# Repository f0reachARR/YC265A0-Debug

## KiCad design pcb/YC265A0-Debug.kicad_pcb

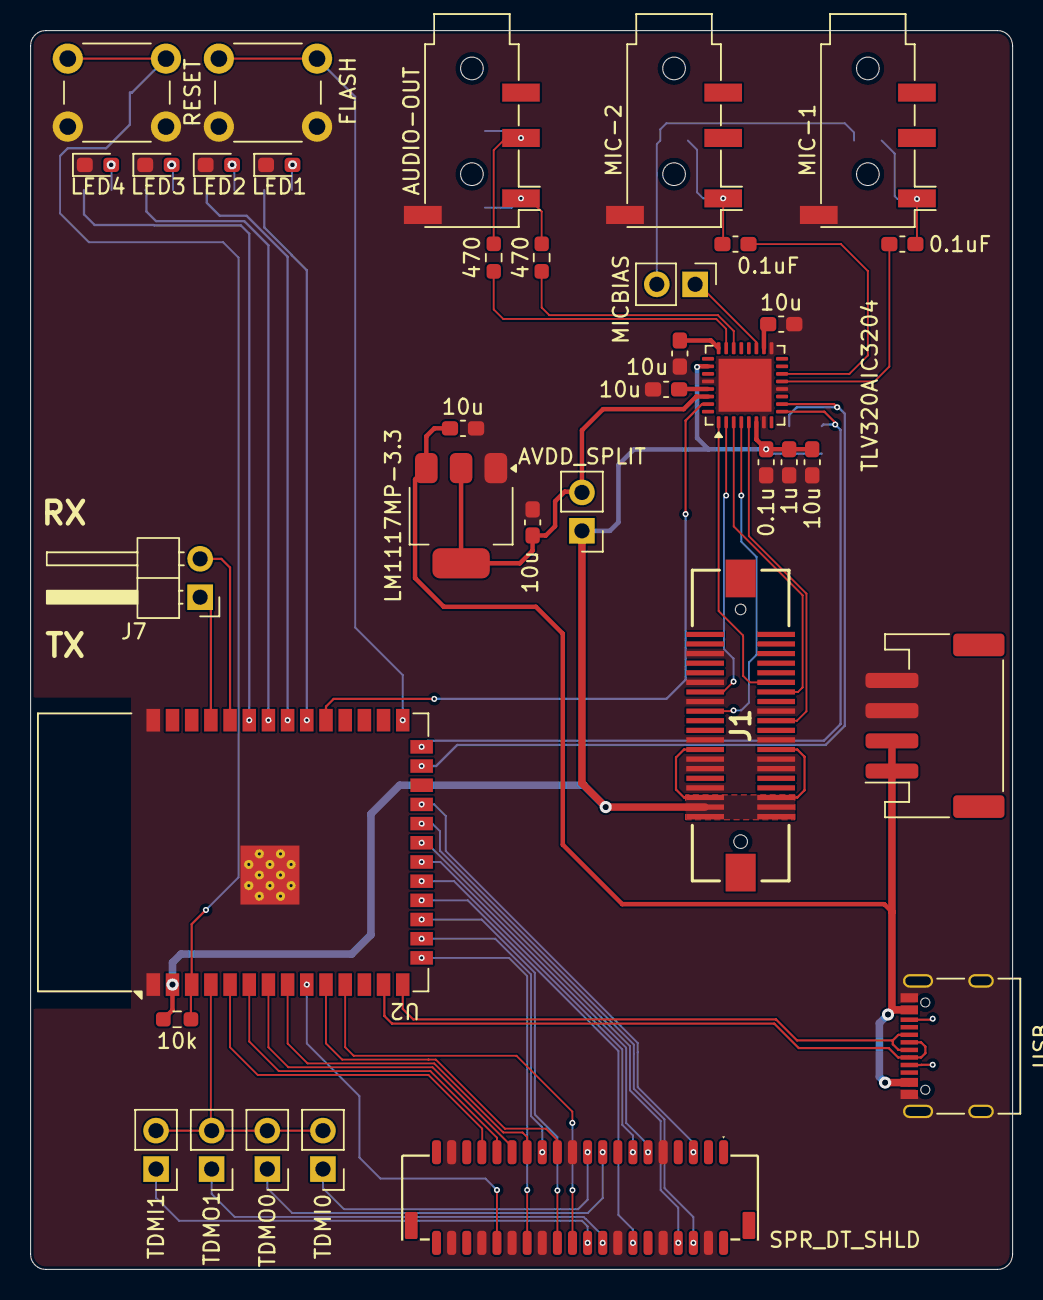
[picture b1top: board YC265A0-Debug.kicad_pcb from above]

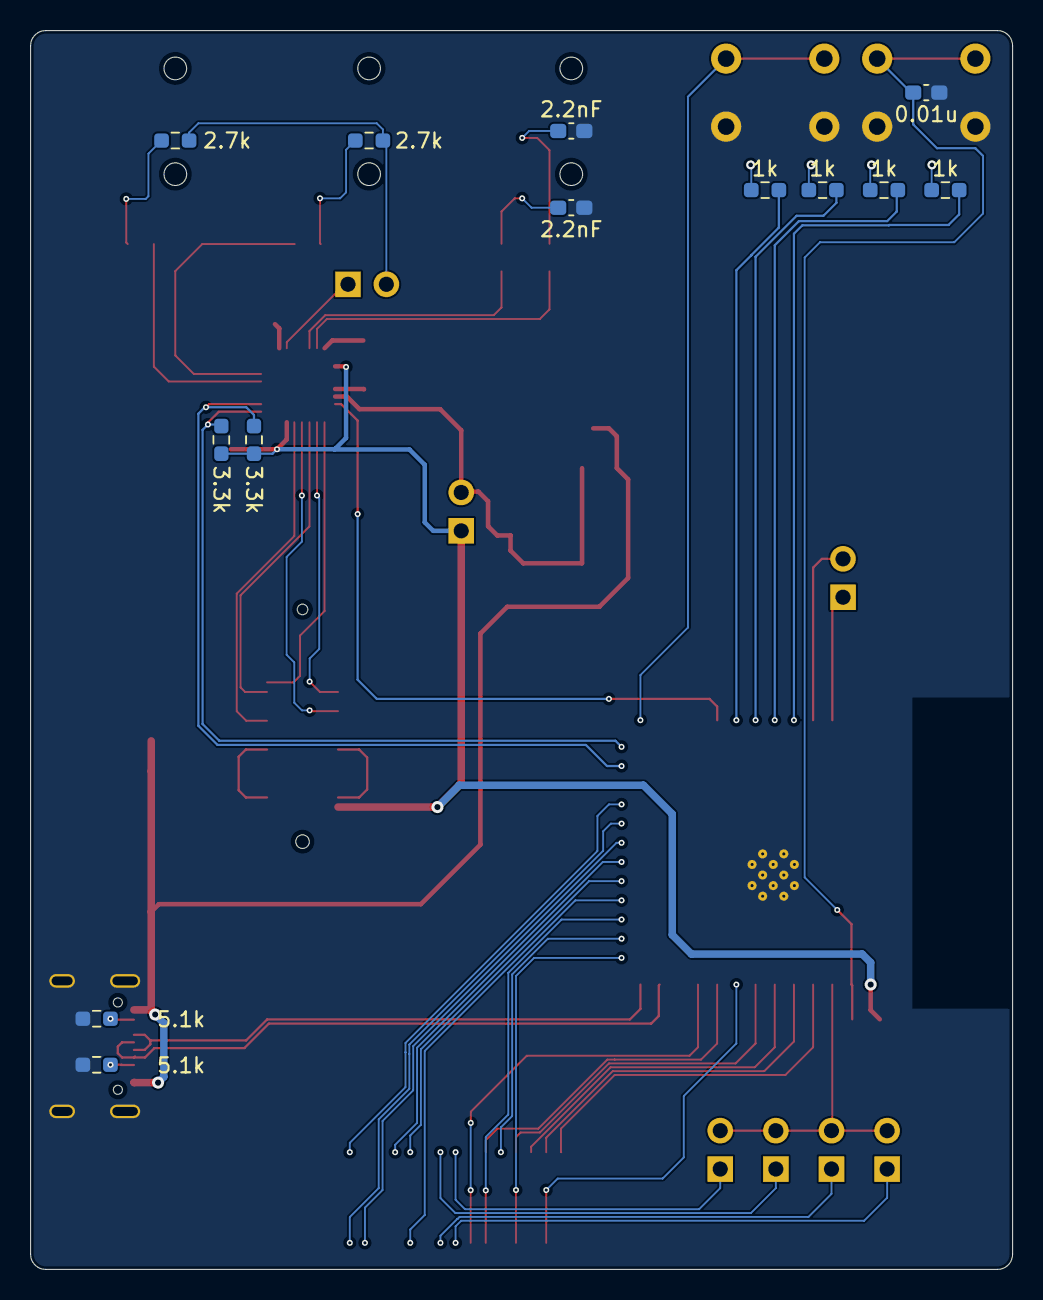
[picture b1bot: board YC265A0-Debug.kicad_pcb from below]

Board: 2 copper layers, 65.0 x 82.0 mm, 49 parts (13 on the bottom side), 62 nets.

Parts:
B1: SPR_DT_SHLD; JST_SHD_SM40B-SRDS-G-TF_2x20_P1.0_Right_Angle
C1, C2, C3, C4, C11, C12: 10u; C_0603_1608Metric_Pad1.08x0.95mm_HandSolder
C5: 1u; C_0603_1608Metric_Pad1.08x0.95mm_HandSolder
C6: 0.1u; C_0603_1608Metric_Pad1.08x0.95mm_HandSolder
C7, C8: 2.2nF; C_0603_1608Metric_Pad1.08x0.95mm_HandSolder
C9, C10: 0.1uF; C_0603_1608Metric_Pad1.08x0.95mm_HandSolder
C13: 0.01u; C_0603_1608Metric_Pad1.08x0.95mm_HandSolder
D1: LED1; LED_0603_1608Metric_Pad1.05x0.95mm_HandSolder
D2: LED2; LED_0603_1608Metric_Pad1.05x0.95mm_HandSolder
D3: LED3; LED_0603_1608Metric_Pad1.05x0.95mm_HandSolder
D4: LED4; LED_0603_1608Metric_Pad1.05x0.95mm_HandSolder
J1: SPR_DT_BC; 529010474
J2: AUDIO-OUT; Jack_3.5mm_PJ320D_Horizontal
J3: MIC-1; Jack_3.5mm_PJ320D_Horizontal
J4: MIC-2; Jack_3.5mm_PJ320D_Horizontal
J5: USB; USB_C_Receptacle_Palconn_UTC16-G
J6: PWR5V; JST_PH_S4B-PH-SM4-TB_1x04-1MP_P2.00mm_Horizontal
J7: Conn_01x02_Pin; PinHeader_1x02_P2.54mm_Horizontal
JP1: MICBIAS; PinHeader_1x02_P2.54mm_Vertical
JP2: AVDD_SPLIT; PinHeader_1x02_P2.54mm_Vertical
JP3: TDMO0; PinHeader_1x02_P2.54mm_Vertical
JP4: TDMO1; PinHeader_1x02_P2.54mm_Vertical
JP5: TDMI0; PinHeader_1x02_P2.54mm_Vertical
JP6: TDMI1; PinHeader_1x02_P2.54mm_Vertical
R1, R2: 470; R_0603_1608Metric_Pad0.98x0.95mm_HandSolder
R3, R4: 2.7k; R_0603_1608Metric_Pad0.98x0.95mm_HandSolder
R5, R6: 5.1k; R_0603_1608Metric_Pad0.98x0.95mm_HandSolder
R7: 10k; R_0603_1608Metric_Pad0.98x0.95mm_HandSolder
R8, R9, R10, R11: 1k; R_0603_1608Metric_Pad0.98x0.95mm_HandSolder
R12, R13: 3.3k; R_0603_1608Metric_Pad0.98x0.95mm_HandSolder
SW1: RESET; SW_PUSH_6mm_H8mm
SW2: FLASH; SW_PUSH_6mm_H8mm
U1: TLV320AIC3204; VQFN-32-1EP_5x5mm_P0.5mm_EP3.5x3.5mm
U2: ESP32-S3-WROOM-1
U3: LM1117MP-3.3; SOT-223-3_TabPin2

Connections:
+3.3V: C4.1, C5.2, C6.2, J1.1 (+3.3VDSW), J1.2 (+3.3VDSW), J1.3 (+3.3VDSW), J1.4 (+3.3VDSW), J1.5 (+3.3VDSW), J1.6 (+3.3VDSW), J1.15 (+5D), J1.16 (+5D), JP2.1 (A), R7.1, R12.2, R13.2, U1.6 (OVIDD), U1.26 (LDOIN), U2.2 (3V3)
+3.3VA: C11.2, JP2.2 (B), U1.30 (LDO_SELECT), U3.2 (VO)
+5V: C12.2, J5.A4 (VBUS), J5.A9 (VBUS), J5.B4 (VBUS), J5.B9 (VBUS), J6.1, J6.2, U3.3 (VI)
/AUDIO_IO/LINEOUT_L: R1.1, U1.22 (LOL)
/AUDIO_IO/LINEOUT_R: R2.2, U1.23 (LOR)
/AUDIO_IO/MIC1_IN: C10.2, U1.13 (IN1_L)
/AUDIO_IO/MIC2_IN: C9.2, U1.14 (IN1_R)
/AUDIO_IO/MICBIAS: JP1.2 (B), R3.2, R4.2
/BCLK: J1.28 (BICK), U1.2 (BCLK)
/CODEC_RESET: U1.31 (~RESET), U2.31 (IO38)
/DIN: J1.24 (I2S-PRE), U1.4 (DIN/MFP1)
/DOUT: J1.21 (I2S-MIC), U1.5 (DOUT/MFP2)
/I2S_ADPCM: B1.11 (SDO-ADPCM), U2.20 (IO12)
/I2S_BCLK_MCU: B1.6 (BCLK-DT), U2.22 (IO14)
/I2S_IN: JP3.2 (B), JP4.2 (B), JP5.2 (B), JP6.2 (B), U2.4 (IO4)
/I2S_MCLK_MCU: B1.8 (MCLK-DT), U2.21 (IO13)
/I2S_MP3_0: B1.13 (SDO-MP3-0), U2.19 (IO11)
/I2S_MP3_1: B1.14 (SDO-MP3-1), U2.18 (IO10)
/I2S_WCLK_MCU: B1.5 (WCLK-DT), U2.23 (IO21)
/MCLK: J1.29 (MCLK), U1.1 (MCLK_(1))
/MCU/DEBUG_RX: J7.2, U2.36 (RXD0)
/MCU/DEBUG_TX: J7.1, U2.37 (TXD0)
/MCU/EN: C13.1, R7.2, SW1.1, U2.3 (EN)
/MCU/FLASH: SW2.1, U2.27 (IO0)
/MCU/LED1: R8.1, U2.32 (IO39)
/MCU/LED2: R9.1, U2.33 (IO40)
/MCU/LED3: R10.1, U2.34 (IO41)
/MCU/LED4: R11.1, U2.35 (IO42)
/MCU/USBDM: J5.A7 (D-), J5.B7 (D-), U2.13 (USB_D-)
/MCU/USBDP: J5.A6 (D+), J5.B6 (D+), U2.14 (USB_D+)
/SCL: R13.1, U1.9 (SCL/SSZ), U2.26 (IO45)
/SDA: R12.1, U1.10 (SDA/MOSI), U2.25 (IO48)
/TDMI0: B1.19 (TDMI-DVNC0), JP5.1 (A)
/TDMI1: B1.20 (TDMI-DVNC1), JP6.1 (A)
/TDMO0: B1.17 (TDMO-DVNC0), JP3.1 (A)
/TDMO1: B1.18 (TDMO-DVNC1), JP4.1 (A)
/WCLK: J1.27 (LRCK), U1.3 (WCLK)
GND: B1.4 (DGND), B1.9 (DGND), B1.10 (DGND), B1.16 (DGND), B1.21 (DGND), B1.26 (DGND), B1.30 (DGND), B1.34 (DGND), B1.37 (DGND), B1.38 (DGND), C1.2, C2.2, C3.1, C4.2, C5.1, C6.1, C7.2, C8.1, C11.1, C12.1, C13.2, D1.1 (K), D2.1 (K), D3.1 (K), D4.1 (K), J1.8 (GND), J1.11 (GND), J1.12 (GND), J1.13 (GND), J1.14 (GND), J1.17 (GND), J1.18 (GND), J1.23 (GND), J1.26 (GND), J1.30 (GND), J1.36 (GND), J2.S, J3.S, J4.S, J5.A1 (GND), J5.A12 (GND), J5.B1 (GND), J5.B12 (GND), J5.S1 (SHIELD), J6.3, J6.4, R5.2, R6.2, SW1.2, SW2.2, U1.7 (IOVSS), U1.12 (SPI_SELECT), U1.17 (AVSS), U1.28 (DVSS), U1.33 (EP), U2.1 (GND), U2.40 (GND), U2.41 (GND), U3.1 (GND)
MIDI-RX0: B1.22 (ACIA-RXD0), U2.11 (IO18)
MIDI-RX1: B1.24 (ACIA-RXD1), U2.17 (IO9)
MIDI-RX2: B1.27 (ACIA-RXD2), U2.8 (IO15)
MIDI-RX3: B1.31 (ACIA-RXD3), U2.6 (IO6)
MIDI-TX0: B1.23 (ACIA-TXD0), U2.10 (IO17)
MIDI-TX1: B1.25 (ACIA-TXD1), U2.16 (IO46)
MIDI-TX2: B1.28 (ACIA-TXD2), U2.15 (IO3)
MIDI-TX3: B1.29 (ACIA-TXD3), U2.7 (IO7)
MIDI-TX4: B1.32 (ACIA-TXD4), U2.9 (IO16)
MIDI-TX5: B1.33 (ACIA-TXD5), U2.5 (IO5)
unnamed: C7.1, J2.T, R1.2
unnamed: C8.2, J2.R1, R2.1
unnamed: C9.1, J4.T, R3.1
unnamed: C10.1, J3.T, R4.1
unnamed: D1.2 (A), R8.2
unnamed: D2.2 (A), R9.2
unnamed: D3.2 (A), R10.2
unnamed: D4.2 (A), R11.2
unnamed: J5.A5 (CC1), R5.1
unnamed: J5.B5 (CC2), R6.1
unnamed: JP1.1 (A), U1.19 (MICBIAS)
unnamed: C2.1, U1.24 (AVDD)
unnamed: C1.1, U1.29 (DVDD)
unnamed: C3.2, U1.18 (REF)

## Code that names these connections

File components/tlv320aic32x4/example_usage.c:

/**
 * @file example_usage.c
 * @brief TLV320AIC32x4 usage example
 *
 * This example demonstrates how to initialize and use the TLV320AIC32x4 audio codec
 * with ESP-IDF and ESP32's I2S peripheral.
 */

#include <stdio.h>
#include <math.h>
#include "freertos/FreeRTOS.h"
#include "freertos/task.h"
#include "driver/i2c_master.h"
#include "driver/i2s_std.h"
#include "esp_log.h"
#include "tlv320aic32x4.h"

static const char *TAG = "AIC32X4_EXAMPLE";

/* GPIO definitions - adjust these for your hardware */
#define I2C_MASTER_SCL_IO           22      /* GPIO number for I2C master clock */
#define I2C_MASTER_SDA_IO           21      /* GPIO number for I2C master data  */
#define I2C_MASTER_FREQ_HZ          100000  /* I2C master clock frequency */

#define I2S_BCK_IO                  26      /* GPIO for I2S bit clock */
#define I2S_WS_IO                   25      /* GPIO for I2S word select (LRCLK) */
#define I2S_DO_IO                   27      /* GPIO for I2S data out (to codec DIN) */
#define I2S_DI_IO                   35      /* GPIO for I2S data in (from codec DOUT) */
#define I2S_MCLK_IO                 0       /* GPIO for master clock (MCLK) */

#define CODEC_I2C_ADDR              0x18    /* Default I2C address */
#define CODEC_RESET_GPIO            -1      /* Set to actual GPIO if reset is connected */

#define SAMPLE_RATE                 48000   /* Audio sample rate */
#define BITS_PER_SAMPLE             16      /* Bits per sample */

/* I2S channel handle */
static i2s_chan_handle_t tx_chan = NULL;
static i2s_chan_handle_t rx_chan = NULL;

/* I2C bus handle */
static i2c_master_bus_handle_t i2c_bus_handle = NULL;

/**
 * @brief Initialize I2C master
 */
static esp_err_t i2c_master_init(i2c_master_bus_handle_t *bus_handle)
{
    i2c_master_bus_config_t i2c_bus_config = {
        .clk_source = I2C_CLK_SRC_DEFAULT,
        .i2c_port = I2C_NUM_0,
        .scl_io_num = I2C_MASTER_SCL_IO,
        .sda_io_num = I2C_MASTER_SDA_IO,
        .glitch_ignore_cnt = 7,
        .flags.enable_internal_pullup = true,
    };

    esp_err_t ret = i2c_new_master_bus(&i2c_bus_config, bus_handle);
    if (ret != ESP_OK) {
        ESP_LOGE(TAG, "I2C master bus init failed");
        return ret;
    }

    ESP_LOGI(TAG, "I2C master initialized");
    return ESP_OK;
}

/**
 * @brief Initialize I2S
 */
static esp_err_t i2s_driver_init(void)
{
    /* Create I2S channel */
    i2s_chan_config_t chan_cfg = I2S_CHANNEL_DEFAULT_CONFIG(I2S_NUM_0, I2S_ROLE_MASTER);
    esp_err_t ret = i2s_new_channel(&chan_cfg, &tx_chan, &rx_chan);
    if (ret != ESP_OK) {
        ESP_LOGE(TAG, "Failed to create I2S channel");
        return ret;
    }

    /* Configure I2S standard mode */
    i2s_std_config_t std_cfg = {
        .clk_cfg = {
            .sample_rate_hz = SAMPLE_RATE,
            .clk_src = I2S_CLK_SRC_DEFAULT,
            .mclk_multiple = I2S_MCLK_MULTIPLE_256,
        },
        .slot_cfg = I2S_STD_PHILIPS_SLOT_DEFAULT_CONFIG(I2S_DATA_BIT_WIDTH_16BIT, I2S_SLOT_MODE_STEREO),
        .gpio_cfg = {
            .mclk = I2S_MCLK_IO,
            .bclk = I2S_BCK_IO,
            .ws = I2S_WS_IO,
            .dout = I2S_DO_IO,
            .din = I2S_DI_IO,
            .invert_flags = {
                .mclk_inv = false,
                .bclk_inv = false,
                .ws_inv = false,
            },
        },
    };

    ret = i2s_channel_init_std_mode(tx_chan, &std_cfg);
    if (ret != ESP_OK) {
        ESP_LOGE(TAG, "Failed to init I2S TX channel");
        return ret;
    }

    ret = i2s_channel_init_std_mode(rx_chan, &std_cfg);
    if (ret != ESP_OK) {
        ESP_LOGE(TAG, "Failed to init I2S RX channel");
        return ret;
    }

    /* Enable channels */
    ret = i2s_channel_enable(tx_chan);
    if (ret != ESP_OK) {
        ESP_LOGE(TAG, "Failed to enable I2S TX channel");
        return ret;
    }

    ret = i2s_channel_enable(rx_chan);
    if (ret != ESP_OK) {
        ESP_LOGE(TAG, "Failed to enable I2S RX channel");
        return ret;
    }

    ESP_LOGI(TAG, "I2S driver initialized");
    return ESP_OK;
}

/**
 * @brief Initialize TLV320AIC32x4 codec
 */
static esp_err_t codec_init(aic32x4_handle_t **handle, i2c_master_bus_handle_t bus_handle)
{
    aic32x4_config_t codec_config = {
        .i2c_bus_handle = bus_handle,
        .i2c_addr = CODEC_I2C_ADDR,
        .mclk_freq = AIC32X4_FREQ_12000000,  /* Adjust based on your MCLK */
        .sample_rate = SAMPLE_RATE,
        .word_length = BITS_PER_SAMPLE,
        .audio_format = AIC32X4_I2S_MODE,
        .master_mode = false,                /* ESP32 is master */
        .power_cfg = AIC32X4_PWR_AVDD_DVDD_WEAK_DISABLE,
        .micpga_routing = 0,
        .swap_dacs = false,
        .reset_gpio = CODEC_RESET_GPIO,
    };

    esp_err_t ret = aic32x4_init(&codec_config, handle);
    if (ret != ESP_OK) {
        ESP_LOGE(TAG, "Failed to initialize codec");
        return ret;
    }

    /* Set DAC volume (0 = max, 63 = min, in 0.5dB steps) */
    ret = aic32x4_set_dac_volume(*handle, 10, 10);
    if (ret != ESP_OK) {
        ESP_LOGE(TAG, "Failed to set DAC volume");
        return ret;
    }

    /* Unmute DAC */
    ret = aic32x4_set_mute(*handle, false);
    if (ret != ESP_OK) {
        ESP_LOGE(TAG, "Failed to unmute DAC");
        return ret;
    }

    /* Set ADC volume (0 = min, 40 = max) */
    ret = aic32x4_set_adc_volume(*handle, 20, 20);
    if (ret != ESP_OK) {
        ESP_LOGE(TAG, "Failed to set ADC volume");
        return ret;
    }

    ESP_LOGI(TAG, "Codec initialized successfully");
    return ESP_OK;
}

/**
 * @brief Audio playback example task
 */
static void audio_playback_task(void *pvParameters)
{
    aic32x4_handle_t *codec_handle = (aic32x4_handle_t *)pvParameters;

    /* Generate a simple 1kHz sine wave */
    const int sample_count = SAMPLE_RATE / 1000;  /* 1ms worth of samples */
    int16_t *samples = malloc(sample_count * 2 * sizeof(int16_t));  /* Stereo */

    if (samples == NULL) {
        ESP_LOGE(TAG, "Failed to allocate sample buffer");
        vTaskDelete(NULL);
        return;
    }

    /* Generate sine wave */
    for (int i = 0; i < sample_count; i++) {
        float sample = sin(2.0 * M_PI * 1000.0 * i / SAMPLE_RATE) * 16384.0;
        samples[i * 2] = (int16_t)sample;      /* Left channel */
        samples[i * 2 + 1] = (int16_t)sample;  /* Right channel */
    }

    ESP_LOGI(TAG, "Starting audio playback (1kHz sine wave)");

    size_t bytes_written;
    while (1) {
        /* Write samples to I2S */
        esp_err_t ret = i2s_channel_write(tx_chan, samples,
                                          sample_count * 2 * sizeof(int16_t),
                                          &bytes_written, portMAX_DELAY);
        if (ret != ESP_OK) {
            ESP_LOGE(TAG, "I2S write failed");
            break;
        }
    }

    free(samples);
    vTaskDelete(NULL);
}

/**
 * @brief Audio loopback example task (ADC -> DAC)
 */
static void audio_loopback_task(void *pvParameters)
{
    aic32x4_handle_t *codec_handle = (aic32x4_handle_t *)pvParameters;

    const int buffer_size = 1024;
    int16_t *buffer = malloc(buffer_size * sizeof(int16_t));

    if (buffer == NULL) {
        ESP_LOGE(TAG, "Failed to allocate buffer");
        vTaskDelete(NULL);
        return;
    }

    ESP_LOGI(TAG, "Starting audio loopback (ADC -> DAC)");

    size_t bytes_read, bytes_written;
    while (1) {
        /* Read from ADC */
        esp_err_t ret = i2s_channel_read(rx_chan, buffer,
                                         buffer_size * sizeof(int16_t),
                                         &bytes_read, portMAX_DELAY);
        if (ret != ESP_OK) {
            ESP_LOGE(TAG, "I2S read failed");
            break;
        }

        /* Write to DAC */
        ret = i2s_channel_write(tx_chan, buffer, bytes_read,
                               &bytes_written, portMAX_DELAY);
        if (ret != ESP_OK) {
            ESP_LOGE(TAG, "I2S write failed");
            break;
        }
    }

    free(buffer);
    vTaskDelete(NULL);
}

/**
 * @brief Main application
 */
void app_main(void)
{
    ESP_LOGI(TAG, "TLV320AIC32x4 Example Starting");

    /* Initialize I2C */
    ESP_ERROR_CHECK(i2c_master_init(&i2c_bus_handle));

    /* Initialize I2S */
    ESP_ERROR_CHECK(i2s_driver_init());

    /* Initialize codec */
    aic32x4_handle_t *codec_handle = NULL;
    ESP_ERROR_CHECK(codec_init(&codec_handle, i2c_bus_handle));

    /* Choose one of the following tasks */

    /* Option 1: Play 1kHz sine wave */
    // xTaskCreate(audio_playback_task, "audio_playback", 4096, codec_handle, 5, NULL);

    /* Option 2: Loopback (record and playback simultaneously) */
    xTaskCreate(audio_loopback_task, "audio_loopback", 4096, codec_handle, 5, NULL);

    ESP_LOGI(TAG, "Example running");
}

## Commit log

2025-11-13 add midi conn
2025-11-14 add bc
2025-12-05 progress
2026-01-30 sample 1
2026-01-30 rename pcb dir
2026-01-30 tlv320 drv
2026-01-30 remove reference driver
2026-01-31 support long RMT RX sequences by storing received symbols in a separate buffer.
2026-01-31 overflow check
